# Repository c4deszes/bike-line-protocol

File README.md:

# LINE protocol

> LINE is a bus type protocol that uses a single controller, it's based on the LIN protocol used in
> automotive products and extends the frame length and number of frames.

## Usage

The project includes a CMake based environment that can be included as a subproject. A function call is used to instantiate the library in a way
that's unique to the application.

```cmake
include(tools/cmake/CPM.cmake)
CPMAddPackage("gh:c4deszes/bike-line-protocol#master")

line_codegen(TARGET protocol-stack
             CONFIG config
             ADAPTER
)

add_executable(MyApp src/main.c)
target_link_libraries(MyApp PUBLIC protocol-stack)
```

A code generation configuration is required, a single instance multiple
network definitions and multiple nodes can be used.

```json
{
    "Network": {
        "channel": 0,
        "rxBufferSize": 128,
        "txBufferSize": 128,
        "oneWire": true,
        "network": "multi_node_network.json",
        "nodes": {
            "Peripheral1": {
                "enabled": true,
                "diagnostics": {
                    "channel": 0,
                    "enabled": true,
                    "initAddress": true
                }
            },
            "Peripheral2": {
                "enabled": true,
                "diagnostics": {
                    "channel": 1,
                    "enabled": true,
                    "initAddress": true
                }
            }
        }
    }
}
```

## Building

The library only has interface and test targets, run the C library tests using
`cmake --workflow --preset workflow-test`.

Documentation is built using Sphinx with doxygen, that can be generated using
cmake as well by running `cmake --workflow --preset workflow-docs`.

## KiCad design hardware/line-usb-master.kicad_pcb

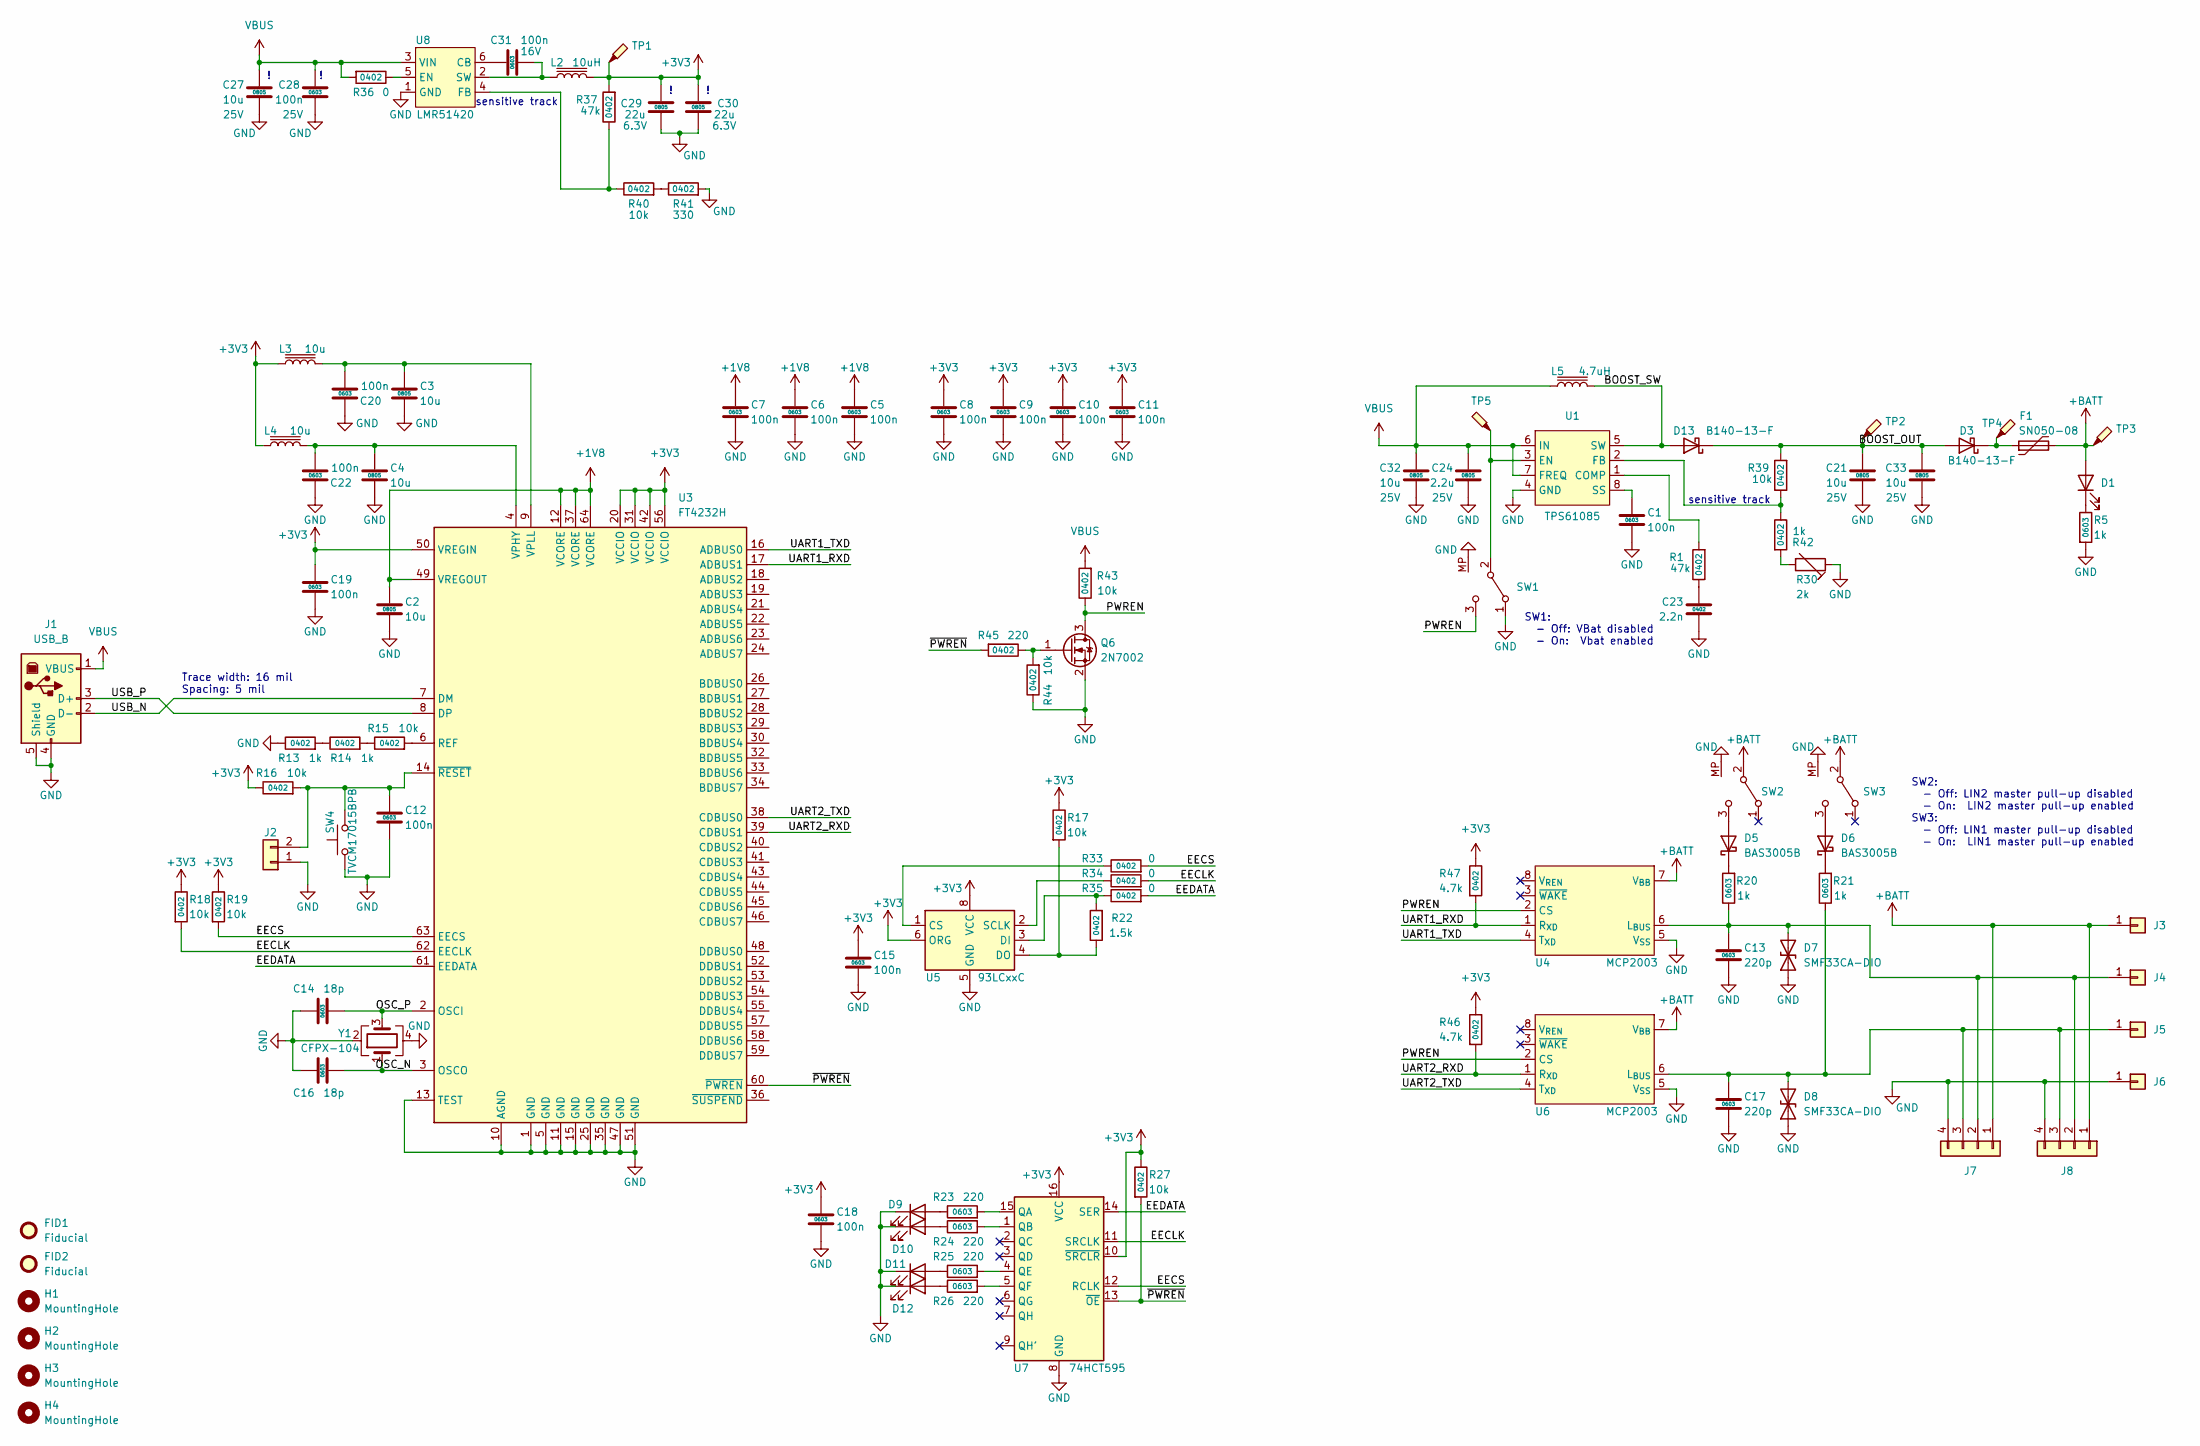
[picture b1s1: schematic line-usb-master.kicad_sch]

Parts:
C1, C5, C6, C7, C8, C9, C10, C11, C12, C15, C18, C19, C20, C22: 100n; C_0603_1608Metric
C2, C3, C4: 10u; C_0805_2012Metric
C13, C17: 220p; C_0603_1608Metric
C14, C16: 18p; C_0603_1608Metric
C21, C27, C32, C33: 10u; C_0805_2012Metric; Rating 25V
C23: 2.2n; C_0402_1005Metric
C24: 2.2u; C_0805_2012Metric; Rating 25V
C28: 100n; C_0603_1608Metric; Rating 25V
C29, C30: 22u; C_0805_2012Metric; Rating 6.3V
C31: 100n; C_0603_1608Metric; Rating 16V
D1, D9, D10, D11, D12: LED; LED_0603_1608Metric
D3, D13: B140-13-F; D_SMA
D5, D6: BAS3005B; D_SOD-523
D7, D8: SMF33CA-DIO; D_SMF
F1: SN050-08; Fuse_1206_3216Metric
FID1, FID2: Fiducial; Fiducial_1mm_Mask2mm
H1, H2, H3, H4: MountingHole; MountingHole_2.2mm_M2
J1: USB_B; USB_B_Lumberg_2411_02_Horizontal
J2: Conn_01x02; PinHeader_1x02_P2.54mm_Vertical
J3: Banana; BananaJack_15.3mm
J4, J5, J6: Conn_01x01; BananaJack_15.3mm
J7, J8: Conn_01x04; PinHeader_1x04_P2.54mm_Vertical
L2: 10uH; HPI0530
L3, L4: 10u; L_0805_2012Metric
L5: 4.7uH; HPI0530
Q6: 2N7002; SOT-23
R1, R37: 47k; R_0402_1005Metric
R5, R20, R21: 1k; R_0603_1608Metric
R13, R14, R42: 1k; R_0402_1005Metric
R15, R16, R17, R18, R19, R27, R39, R40, R43, R44: 10k; R_0402_1005Metric
R22: 1.5k; R_0402_1005Metric
R23, R24, R25, R26: 220; R_0603_1608Metric
R30: 2k; 3305SMD-POT
R33, R34, R35, R36: 0; R_0402_1005Metric
R41: 330; R_0402_1005Metric
R45: 220; R_0402_1005Metric
R46, R47: 4.7k; R_0402_1005Metric
SW1, SW2, SW3: SW_SPDT; S3PCBKP
SW4: TVCM17015BPB; SW_SPST_SKQG_WithStem
TP1, TP2, TP3, TP4, TP5: TestPoint_Probe; TestPoint_Pad_D1.5mm
U1: TPS61085; TSSOP-8_3x3mm_P0.65mm
U3: FT4232H; LQFP-64_10x10mm_P0.5mm
U4, U6: MCP2003; SOIC-8_3.9x4.9mm_P1.27mm
U5: 93LCxxC; SO-8_3.9x4.9mm_P1.27mm
U7: 74HCT595; SO-16_3.9x9.9mm_P1.27mm
U8: LMR51420; SOT-23-6
Y1: CFPX-104; Crystal_SMD_5032-4Pin_5.0x3.2mm

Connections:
+1V8: C2.1, C5.1, C6.1, C7.1, U3.12 (VCORE), U3.37 (VCORE), U3.49 (VREGOUT), U3.64 (VCORE)
+3V3: C8.1, C9.1, C10.1, C11.1, C15.1, C18.1, C19.1, C29.2, C30.2, L2.2, L3.1, L4.1, R16.1, R17.1, R18.1, R19.1, R27.1, R37.2, R46.1, R47.1, TP1.1, U3.20 (VCCIO), U3.31 (VCCIO), U3.42 (VCCIO), U3.50 (VREGIN), U3.56 (VCCIO), U5.6 (ORG), U5.8 (VCC), U7.10 (~SRCLR), U7.16 (VCC)
+BATT: D1.2 (A), F1.2, J3.1, J7.1, J8.1, SW2.2 (B), SW3.2 (B), TP3.1, U4.7 (V_{BB}), U6.7 (V_{BB})
/BOOST_OUT: C21.2, C33.2, D3.2 (A), D13.1 (K), R39.2, TP2.1
/BOOST_SW: D13.2 (A), L5.2, U1.5 (SW)
/EECLK: R18.2, R34.2, U3.62 (EECLK), U7.11 (SRCLK)
/EECS: R19.2, R33.2, U3.63 (EECS), U7.12 (RCLK)
/EEDATA: R35.2, U3.61 (EEDATA), U7.14 (SER)
/OSC_N: C16.2, U3.3 (OSCO), Y1.1
/OSC_P: C14.2, U3.2 (OSCI), Y1.3
/PWREN: Q6.3 (D), R43.1, SW1.3 (C), U4.2 (CS), U6.2 (CS)
/UART1_RXD: R47.2, U3.17 (ADBUS1), U4.1 (R_{XD})
/UART1_TXD: U3.16 (ADBUS0), U4.4 (T_{XD})
/UART2_RXD: R46.2, U3.39 (CDBUS1), U6.1 (R_{XD})
/UART2_TXD: U3.38 (CDBUS0), U6.4 (T_{XD})
/USB_N: J1.2 (D-), U3.7 (DM)
/USB_P: J1.3 (D+), U3.8 (DP)
/~PWREN: R27.2, R45.2, U3.60 (~PWREN), U7.13 (~OE)
GND: C1.2, C2.2, C3.2, C4.2, C5.2, C6.2, C7.2, C8.2, C9.2, C10.2, C11.2, C12.2, C13.2, C14.1, C15.2, C16.1, C17.2, C18.2, C19.2, C20.1, C21.1, C22.1, C23.1, C24.1, C27.1, C28.2, C29.1, C30.1, C32.1, C33.1, D7.1 (A1), D8.1 (A1), D9.1 (K), D10.1 (K), D11.1 (K), D12.1 (K), J1.4 (GND), J1.5 (Shield), J2.1, J6.1, J7.4, J8.4, Q6.2 (S), R5.2, R13.1, R30.1, R41.2, R44.1, SW1.1 (A), SW1.MP, SW2.MP, SW3.MP, SW4.1, U1.4 (GND), U3.1 (GND), U3.5 (GND), U3.10 (AGND), U3.11 (GND), U3.13 (TEST), U3.15 (GND), U3.25 (GND), U3.35 (GND), U3.47 (GND), U3.51 (GND), U4.5 (V_{SS}), U5.5 (GND), U6.5 (V_{SS}), U7.8 (GND), U8.1 (GND), Y1.2, Y1.4
unnamed: C23.2, R1.1
unnamed: D1.1 (K), R5.1
unnamed: D3.1 (K), F1.1, TP4.1
unnamed: D5.2 (A), SW2.3 (C)
unnamed: D5.1 (K), R20.2
unnamed: D6.2 (A), SW3.3 (C)
unnamed: D6.1 (K), R21.2
unnamed: C13.1, D7.2 (A2), J4.1, J7.2, J8.2, R20.1, U4.6 (L_{BUS})
unnamed: C17.1, D8.2 (A2), J5.1, J7.3, J8.3, R21.1, U6.6 (L_{BUS})
unnamed: D9.2 (A), R23.1
unnamed: D10.2 (A), R24.1
unnamed: D11.2 (A), R25.1
unnamed: D12.2 (A), R26.1
unnamed: C12.1, J2.2, R16.2, SW4.2, U3.14 (~RESET)
unnamed: Q6.1 (G), R44.2, R45.1
unnamed: R13.2, R14.1
unnamed: R14.2, R15.1
unnamed: R30.2, R42.2
unnamed: R40.2, R41.1
unnamed: SW1.2 (B), TP5.1, U1.3 (EN)
unnamed: R1.2, U1.1 (COMP)
unnamed: R39.1, R42.1, U1.2 (FB)
unnamed: C1.1, U1.8 (SS)
unnamed: R15.2, U3.6 (REF)
unnamed: C4.1, C22.2, L4.2, U3.4 (VPHY)
unnamed: C3.1, C20.2, L3.2, U3.9 (VPLL)
unnamed: R33.1, U5.1 (CS)
unnamed: R22.2, R35.1, U5.3 (DI)
unnamed: R17.2, R22.1, U5.4 (DO)
unnamed: R34.1, U5.2 (SCLK)
unnamed: R23.2, U7.15 (QA)
unnamed: R24.2, U7.1 (QB)
unnamed: R25.2, U7.4 (QE)
unnamed: R26.2, U7.5 (QF)
unnamed: C31.2, U8.6 (CB)
unnamed: R36.1, U8.5 (EN)
unnamed: R37.1, R40.1, U8.4 (FB)
unnamed: C31.1, L2.1, U8.2 (SW)
VBUS: C24.2, C27.2, C28.1, C32.2, J1.1 (VBUS), L5.1, R36.2, R43.2, U1.6 (IN), U1.7 (FREQ), U8.3 (VIN)

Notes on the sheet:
sensitive track
Trace width: 16 mil Spacing: 5 mil
SW1: - Off: VBat disabled - On: Vbat enabled
SW2: - Off: LIN2 master pull-up disabled - On: LIN2 master pull-up enabled SW3: - Off: LIN1 master pull-up disabled - On: LIN1 master pull-up enabled

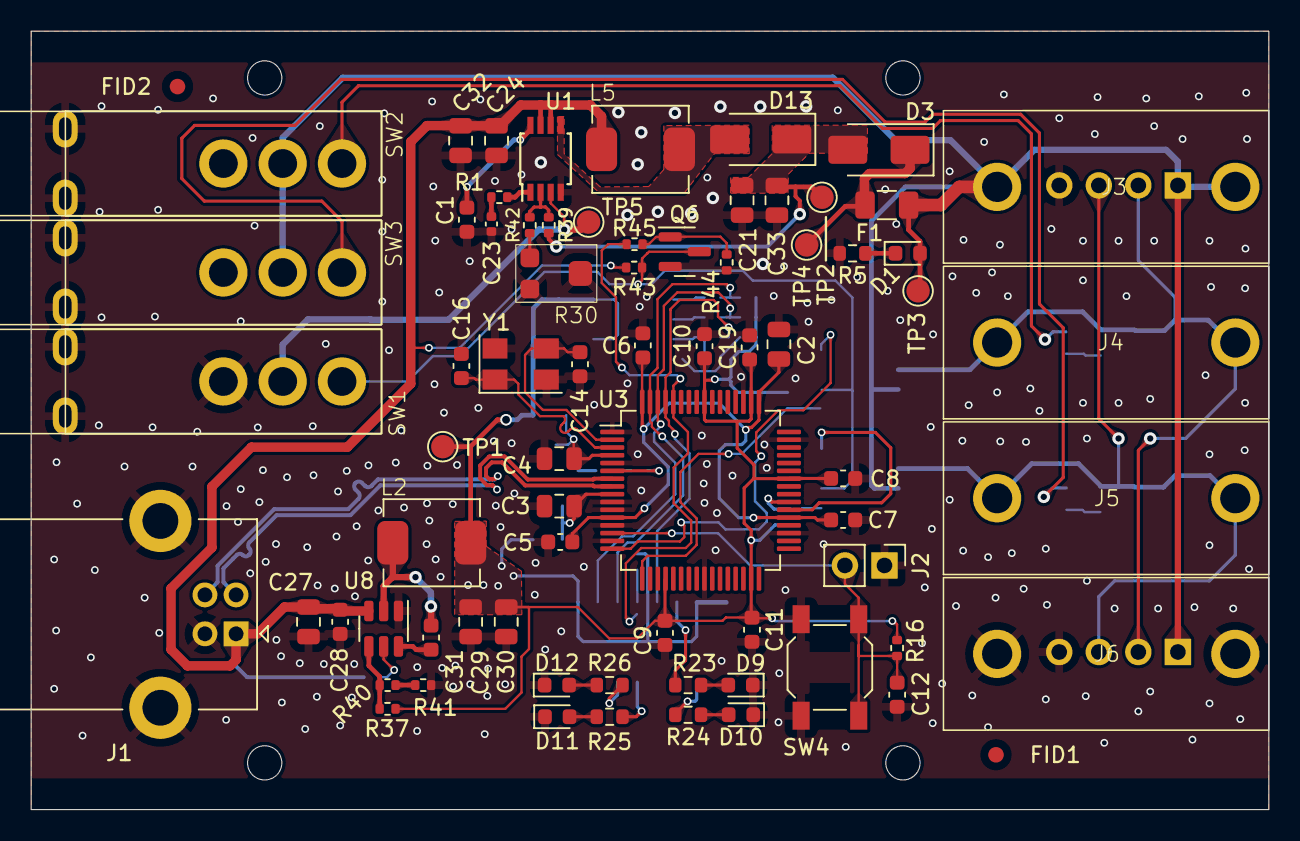
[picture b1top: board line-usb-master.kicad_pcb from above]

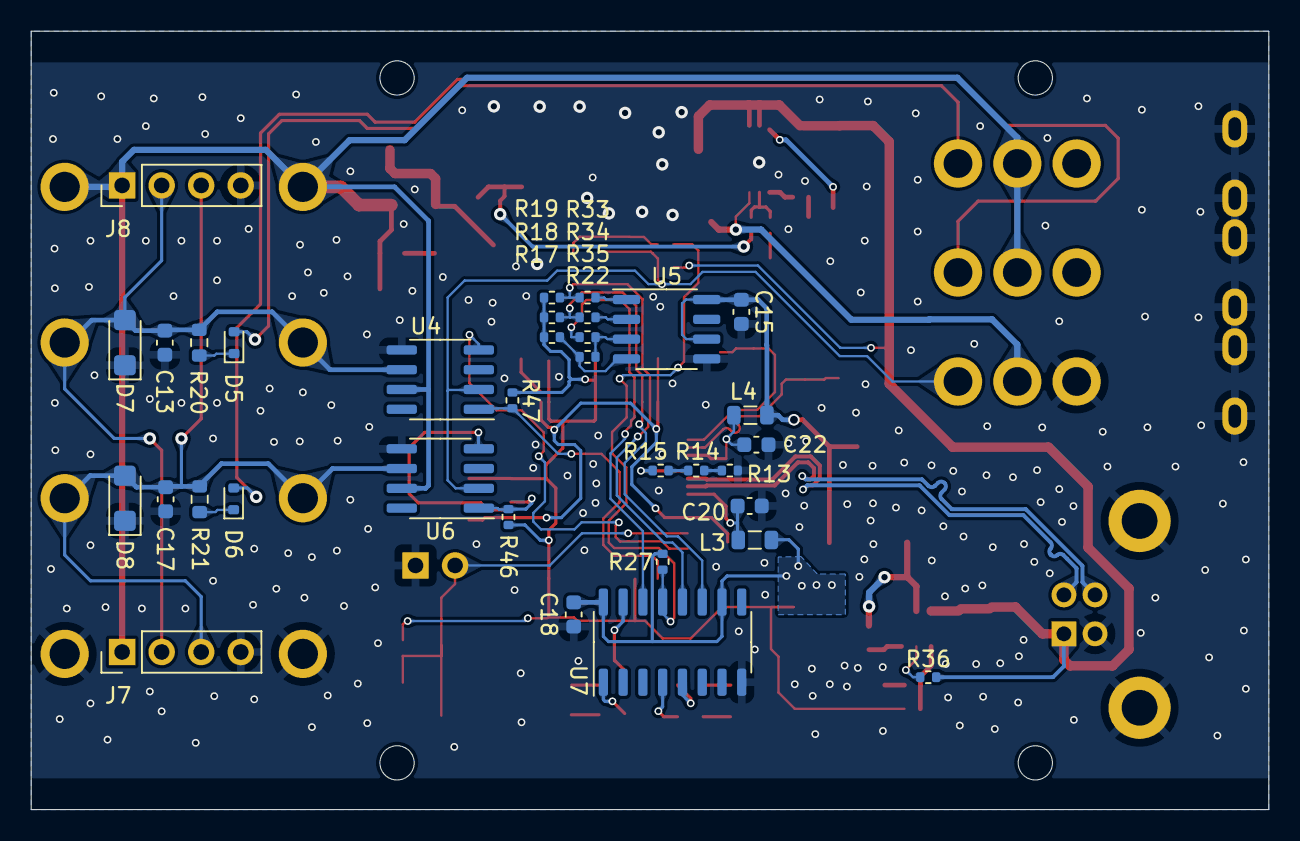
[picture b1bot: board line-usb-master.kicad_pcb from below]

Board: 2 copper layers, 79.5 x 50.0 mm, 111 parts (34 on the bottom side), 58 nets.

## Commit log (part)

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2023-11-15 Documentation
2023-11-15 CI fixes
2023-11-15 Fixing tests Documentation Ipykernel dependency
2023-11-15 Fixing code generator
2023-11-15 Documentation fix
2023-11-15 Setup in CMake environment
2023-11-16 Documentation, default app-transport adapter
2023-11-18 Checksum
2023-11-18 Hardware design
2023-11-19 Wakeup support
2023-11-24 Diagnostics
2023-11-25 Fixing test and CPM compatibility
2023-12-01 CMake integration
2023-12-01 Fixing links
2023-12-02 Fixing, diag. addresses in header
2023-12-19 Signal encoding
    Baudrate in network config
    Encoder implementations
2023-12-26 Working decoding
2023-12-29 Schedule support
    Monitoring config and command
    Fixing request signal packing
2023-12-29 Fixing test cases
    CMake housekeeping, preset updates
2023-12-29 Fixing old network specs.
2023-12-29 Python test fix
2023-12-29 Integration improvements (#1)
    * Project can be integrated using CPM.cmake
    * Documentation improvements
    * Complete Arduino example
    * Hardware design
    * Baudrate info in network
    * Schedule table support
2024-01-01 Transport traffic capture
2024-01-01 Documentation update
2024-01-01 Codegen updates
2024-01-02 Restructure
2024-01-03 Measurement support
    Signals can be recorded, then dumped into csv
    New diagnostic command "conditional change address"
    Fix integer type in bitfield
    Transport no longer waits in one wire mode
2024-01-05 First working UI
2024-01-12 New diag interfaces
    API has empty defaults
2024-01-13 Diag service extension support
2024-01-13 Support for not responding to transport requests
    Fixing diagnostic callback signatures
2024-01-20 Conditional change address support
2024-01-21 Defaults for conditional change address, sw version and power status
2024-01-21 Fixes
2024-01-23 Finalizing
2024-01-23 Arduino sketch fix
2024-01-23 Improvements (#2)
    - Conditional change address diagnostic function
    - Documentation
    - Fixing large signal widths in the generated code
    - Command line interface to do capture data
    - Operation status includes Boot status
    - Empty defaults for API function
2024-02-29 Hardware fixes
    Crystal 4th pin connected to GND
    Removed series resistor from USB lines
    Corrected pullup on EEPROM lines
    Fixes PWREN Mosfet orientation
    Added fiducial
    Added 4 pin connectors for direct wired variant
2024-02-29 Hardware fixes (#3)
    - Crystal 4th pin connected to GND
    - Removed series resistor from USB lines
    - Corrected pullup on EEPROM lines
    - Fixes PWREN Mosfet orientation
    - Added fiducial
    - Added 4 pin connectors for direct wired variant
2024-03-01 Discovery tool
2024-03-01 Plot autorange X axis Plot tool can be called via main Serial ports are discovered on startup
2024-04-14 Support for request flag
2024-07-30 Request frame function
2024-08-04 Renamed sleep to idle
    Added virtual bus and node simulation possibilities
2024-08-04 Fix test cases
2024-08-04 Better Python tools, idle diagnostics and request flags (#4)
    - Adds network discovery tool
    - Plot tool looks better
    - After every request a flag is set for indication
    - Requests can be made by master devices
    - Sleep function has been renamed to idle
2024-08-05 Changes codegen template search
2025-01-05 More details in the error messages
2025-01-05 Initial version of 2's complement encoder
2025-01-05 Self response timeout
2025-01-12 Transport layer multichannel support RX/TX Buffer size can be controlled Functions added for testing purposes
2025-01-12 RX buffer limits respected
2025-01-15 New codegen and multichannel diagnostics
2025-01-18 Updated CMake function
2025-01-18 Fix source list
2025-02-19 Lots of changes
2025-02-20 Diagnostic calls
2025-02-20 Bugfix
2025-02-25 LINE_Transport_WriteRequest is now optional
2025-03-03 Minor changes
2025-03-03 Test fixes
2025-03-03 Arduino sketch update Change in power status scaling
2025-03-03 Hopefully last
2025-03-03 Multichannel support (#5)
    - Transport layer supports multiple channels in parallel
    - Diagnostic layer supports multiple channels and multiple nodes
2025-04-21 Master works without network specified Logging signal values Draft of new scheduling Updating integration document
2025-06-04 Priority aging schedule Unit loaded for formula encoders Master has generic scheduling interface Master has virtual bus support Working node simulation DIscovery tool made into a function Schedule an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
2025-06-22 Most things working
2025-06-22 Docs
2025-06-23 Signal container compatibility with dictionary
2025-06-26 Fixing serial number parsing Reasonably high code coverage
2025-06-26 Fix typo
2025-06-28 Dynamic version from library.properties
2025-06-29 Disable documentation generation
2025-06-29 Python library rework (#6)
    ## Brief
    - Documentation mostly done, C API is also documented
    - Reworked master buffer interfaces (node status and signals)
    - Version number synchronized across all (Python, documentation, CMake
    and Arduino)
    - Some testing done on the Python library
2025-10-18 Adds 3-4pin JWPF bezel
2025-12-29 Executing codegen a bit differently
2025-12-30 Include templates
2025-12-30 Devcontainer
2025-12-30 Needed tools for development
2025-12-30 Updating workflow
2026-01-04 Reverting codegen execution style Sphinx called from venv when used Documentation dependencies corrected, part of the workflow now Including code coverage for both GTest and Pytest Adds devcontainer 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
2026-01-04 Fixing workflow
2026-01-04 Issue with the Ohm character
2026-01-04 New devcontainer approach
2026-01-04 Coverage using different action
2026-01-04 Documentation updates
2026-01-04 Refactor
2026-01-04 Posting summary
2026-01-07 New transport layer initialization process
    Every transport layer instance have configurable buffer sizes
2026-01-11 Working multichannel diagnostics New naming convention for variables Unassign address is called out Testing diagnostic layer
2026-01-11 Application byte packing test
2026-01-11 Communication flow testing
2026-01-11 Initializing request enable and flag
2026-01-11 Multinode Unicast testing
2026-01-11 Changes letter case for request variables
2026-01-12 Signal read, write and request flag macros
2026-01-12 Class definition order
2026-01-12 Buffer size defaults
2026-01-12 FIx Arduino sketch
2026-01-12 Version bump
2026-01-12 Fixing byte packing
2026-01-12 Moved coverage arguments
2026-01-12 Wait for wakeup to be sent
2026-01-30 Improvements to master interface
2026-01-30 Logging
2026-01-31 DIagnostic extension support for simulated peripherals
2026-01-31 Calling unicast handlers
2026-02-08 Separate transport sources
2026-02-08 Fixed one word options
2026-06-06 Readme
2026-06-06 Listener (not working)
2026-06-06 Library updates (#7)
    ## Brief
    - Documentation workflow improvements
    - CMake and other tooling improvements (Code coverage, workflows)
    ## More
    - Documentation updates
    - Code cleanup (linting)
